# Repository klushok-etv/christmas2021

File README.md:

# christmas 2021
The PCB outline can be generated from the included svg file `star template` using the [svg2shenzen](https://github.com/badgeek/svg2shenzhen) plugin.

For the list of To-Do's check [the TODO list](https://github.com/klushok-etv/christmas2021/projects/1), feel free to add any issues or tasks as well!

## current idea
ESP12F has 15 (17 including rx tx) gpio available. There are 45 signals required to controll each color individually. By combining the same color every 5 leds, all leds can be controlled. Issue that remains is the current requirement per GPIO which far exceeds the limit of the pin.
The current can be increased by adding transistors/fets or something like 2 of the ULN2803 and common anode leds.

ESP kicad lib: [https://github.com/jdunmire/kicad-ESP8266](https://github.com/jdunmire/kicad-ESP8266). -> this library has most models but the centers of the pads are located in an odd place. the symbol is also not colored.

## Current design
This design makes use of the APA106 leds which are pincompatible with the pl9823 when pin 1 is attached to pin 4 etc. Both of these led types can be controlled as if they were a WS2812.

The two buttons are reset and io0, required for programming. 
IO0 can also be used as a user input pin.

THT components have been chosen where possible to easy soldering by hand. 
Components with a SMD package are still solderable by hand, using a tweezer is advised.

Power is fed through to the connectors at the top of the pcb, a jst or other connector can be soldered in place to ensure polarity is correct. No reverse polarity protection is in place!

The star can be programmed using the pads on the back. Wires can be soldered to the pads or pogo pins could be used.

The committee might make a custom programmer to ease flashing for the first time after which OTA/wifimanager can be uploaded. An anternative idea for the firmware might be [WLED](https://github.com/Aircoookie/WLED).

## Possible parts
- ESP32 wroom/wrover -> most expensive and biggest option but has plenty of IO, does require a pad to be soldered so hot air is required
- ESP01 -> very few pins but cheap
- ESP M3 -> based on the 8285 chip with low memory and only a few GPIO's but has a small footprint and is cheap
- ESP12F/E -> Good option but almost same price as ESP32 but reduced functionality and soon to be replaced by ESP32-C3 [https://www.aliexpress.com/item/32963951195.html](https://www.aliexpress.com/item/32963951195.html)
- pl9823 led [https://nl.aliexpress.com/item/32963082574.html](https://nl.aliexpress.com/item/32963082574.html)
- APA106 led [https://www.aliexpress.com/item/4001066329177.html](https://www.aliexpress.com/item/4001066329177.html) or diffused [https://www.aliexpress.com/item/32768672866.html](https://www.aliexpress.com/item/32768672866.html)
- buttons for reset and gpio0, 3x6x2.5mm: [https://www.aliexpress.com/item/32696590759.html](https://www.aliexpress.com/item/32696590759.html)
- angled clamp [https://www.aliexpress.com/item/1005002240862072.html](https://www.aliexpress.com/item/1005002240862072.html)
- usb c connectors [https://www.aliexpress.com/item/1005001283294686.html](https://www.aliexpress.com/item/1005001283294686.html)

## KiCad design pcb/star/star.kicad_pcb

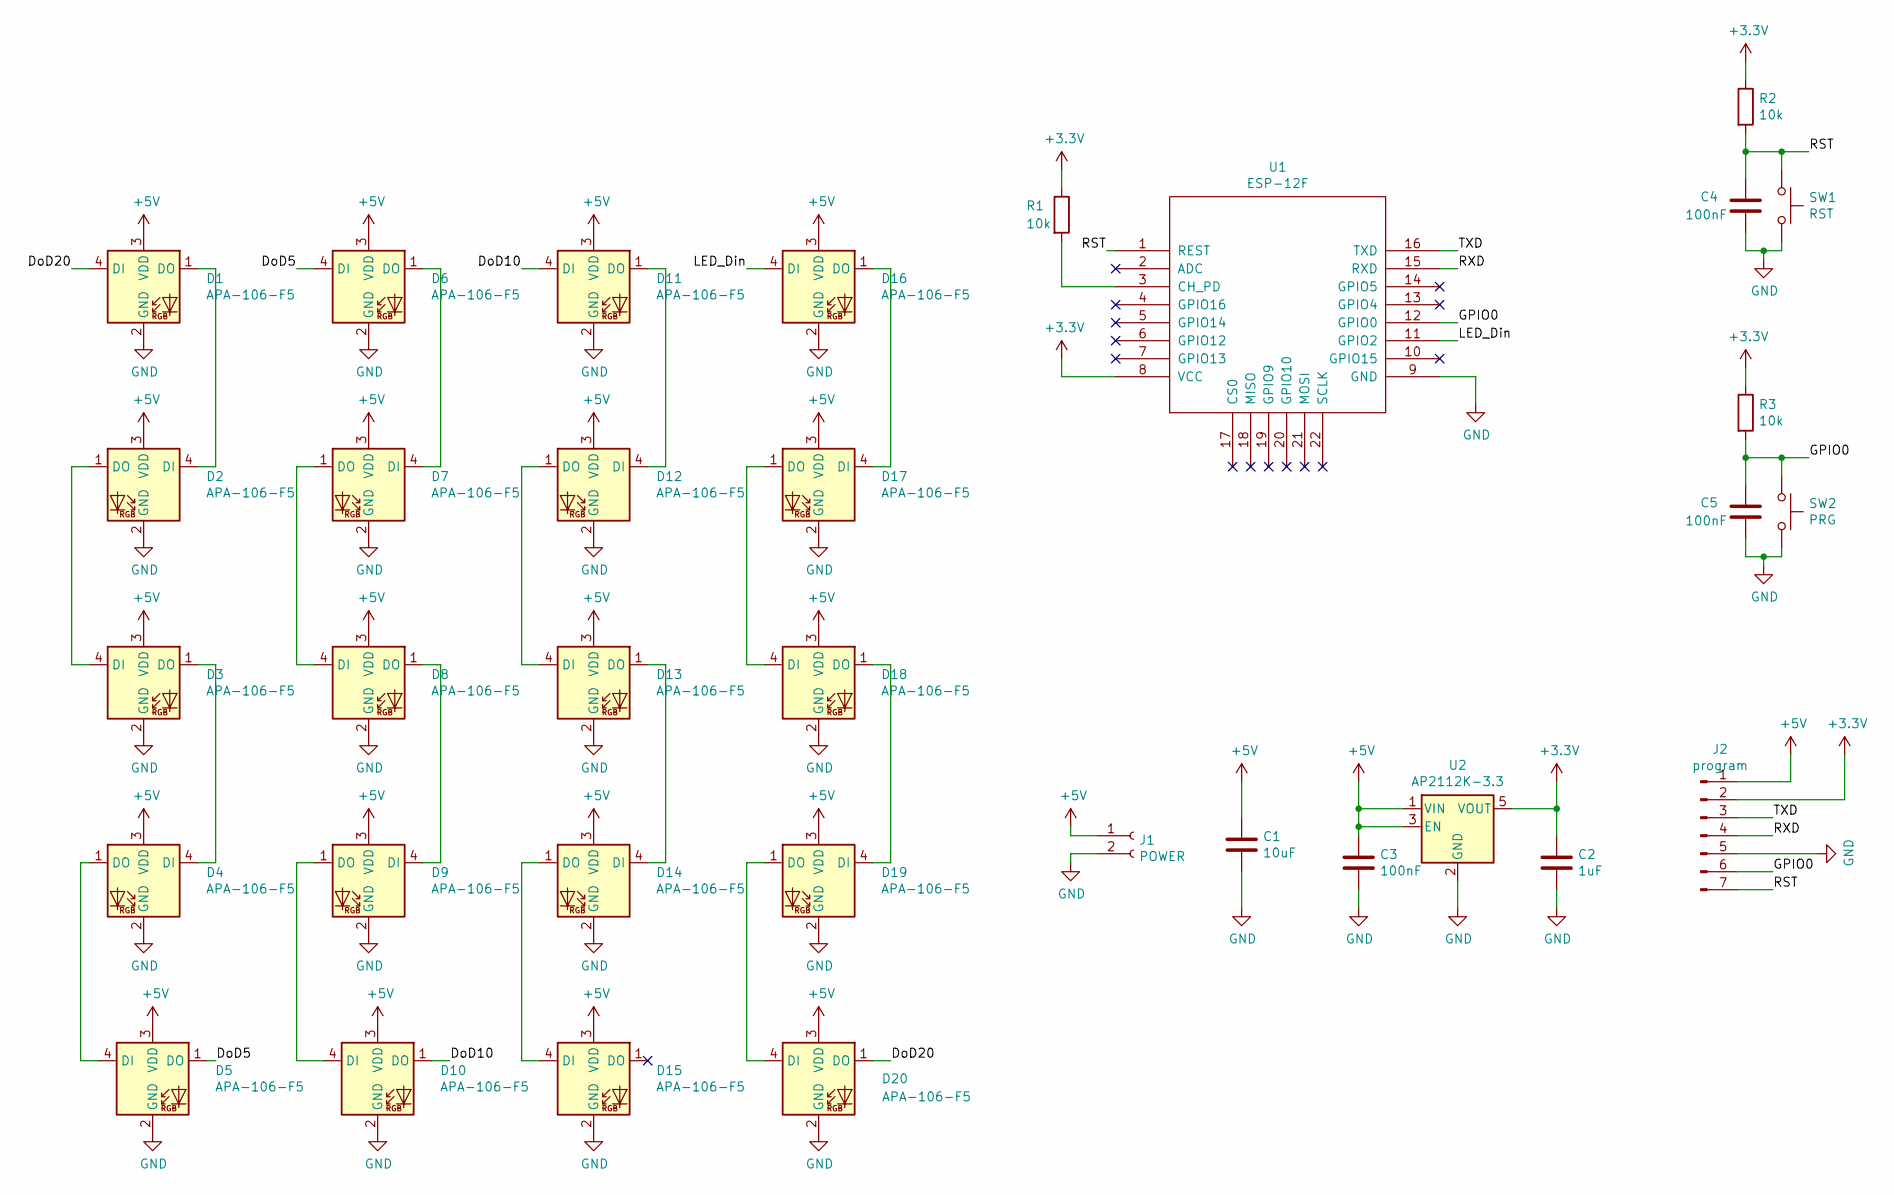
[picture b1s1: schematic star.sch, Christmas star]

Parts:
C1: 10uF; CP_Radial_D5.0mm_P2.50mm
C2: 1uF; CP_Radial_D5.0mm_P2.50mm
C3, C4, C5: 100nF; C_Disc_D5.0mm_W2.5mm_P2.50mm
D1, D2, D3, D4, D5, D6, D7, D8, D9, D10, D11, D12, D13, D14, D15, D16, D17, D18, D19, D20: APA-106-F5; LED_D5.0mm-4_RGB
J1: POWER; PinSocket_1x02_P2.54mm_Vertical
J2: program; conn_01x07_SMD
R1, R2, R3: 10k; R_Axial_DIN0204_L3.6mm_D1.6mm_P7.62mm_Horizontal
SW1: RST; SW_SPST_EVQPE1
SW2: PRG; SW_SPST_EVQPE1
U1: ESP-12F; ESP-12E_SMD
U2: AP2112K-3.3; SOT-23-5

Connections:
+3V3: C2.1, J2.2, R1.1, R2.1, R3.1, U1.8 (VCC), U2.5 (VOUT)
+5V: C1.1, C3.1, D1.3 (VDD), D2.3 (VDD), D3.3 (VDD), D4.3 (VDD), D5.3 (VDD), D6.3 (VDD), D7.3 (VDD), D8.3 (VDD), D9.3 (VDD), D10.3 (VDD), D11.3 (VDD), D12.3 (VDD), D13.3 (VDD), D14.3 (VDD), D15.3 (VDD), D16.3 (VDD), D17.3 (VDD), D18.3 (VDD), D19.3 (VDD), D20.3 (VDD), J1.1, J2.1, U2.1 (VIN), U2.3 (EN)
/DoD5: D5.1 (DO), D6.4 (DI)
/DoD10: D10.1 (DO), D11.4 (DI)
/DoD20: D1.4 (DI), D20.1 (DO)
/GPIO0: C5.2, J2.6, R3.2, SW2.1, U1.12 (GPIO0)
/LED_Din: D16.4 (DI), U1.11 (GPIO2)
/RST: C4.2, J2.7, R2.2, SW1.1, U1.1 (REST)
/RXD: J2.4, U1.15 (RXD)
/TXD: J2.3, U1.16 (TXD)
GND: C1.2, C2.2, C3.2, C4.1, C5.1, D1.2 (GND), D2.2 (GND), D3.2 (GND), D4.2 (GND), D5.2 (GND), D6.2 (GND), D7.2 (GND), D8.2 (GND), D9.2 (GND), D10.2 (GND), D11.2 (GND), D12.2 (GND), D13.2 (GND), D14.2 (GND), D15.2 (GND), D16.2 (GND), D17.2 (GND), D18.2 (GND), D19.2 (GND), D20.2 (GND), J1.2, J2.5, SW1.2, SW2.2, U1.9 (GND), U2.2 (GND)
unnamed: D1.1 (DO), D2.4 (DI)
unnamed: D2.1 (DO), D3.4 (DI)
unnamed: D3.1 (DO), D4.4 (DI)
unnamed: D4.1 (DO), D5.4 (DI)
unnamed: D6.1 (DO), D7.4 (DI)
unnamed: D7.1 (DO), D8.4 (DI)
unnamed: D8.1 (DO), D9.4 (DI)
unnamed: D9.1 (DO), D10.4 (DI)
unnamed: D11.1 (DO), D12.4 (DI)
unnamed: D12.1 (DO), D13.4 (DI)
unnamed: D13.1 (DO), D14.4 (DI)
unnamed: D14.1 (DO), D15.4 (DI)
unnamed: D16.1 (DO), D17.4 (DI)
unnamed: D17.1 (DO), D18.4 (DI)
unnamed: D18.1 (DO), D19.4 (DI)
unnamed: D19.1 (DO), D20.4 (DI)
unnamed: R1.2, U1.3 (CH_PD)

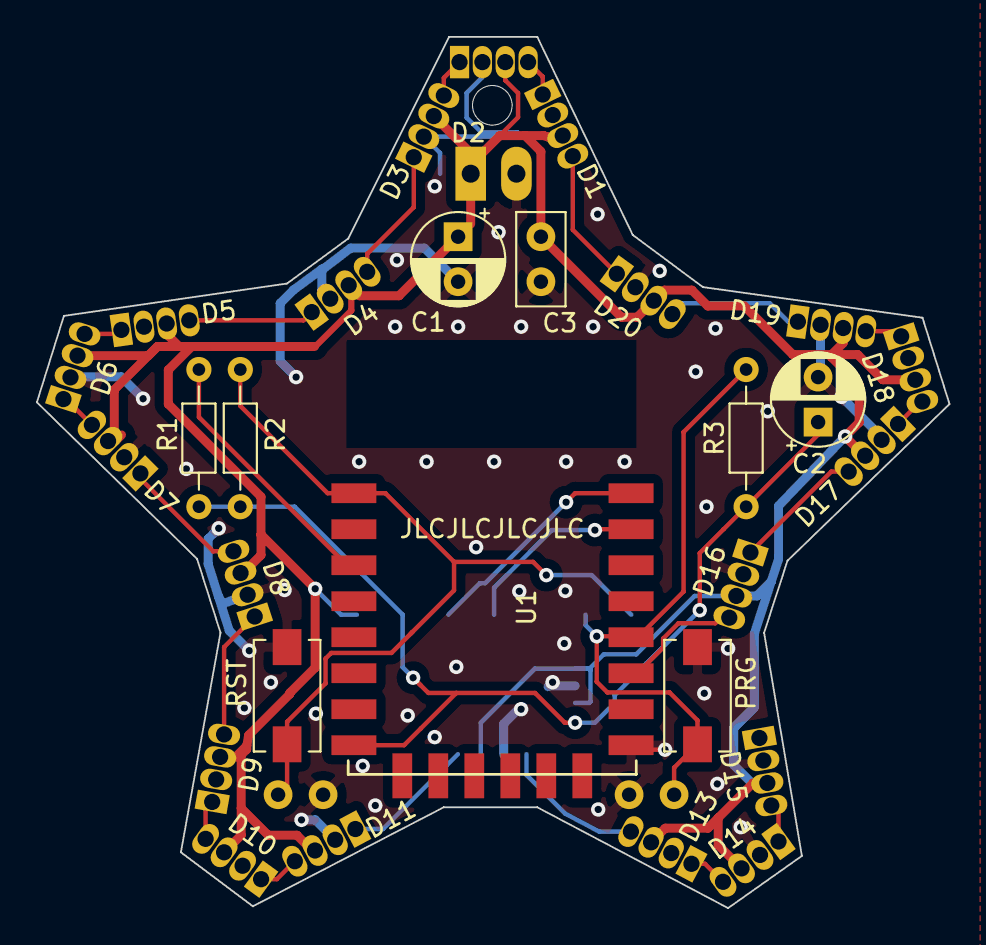
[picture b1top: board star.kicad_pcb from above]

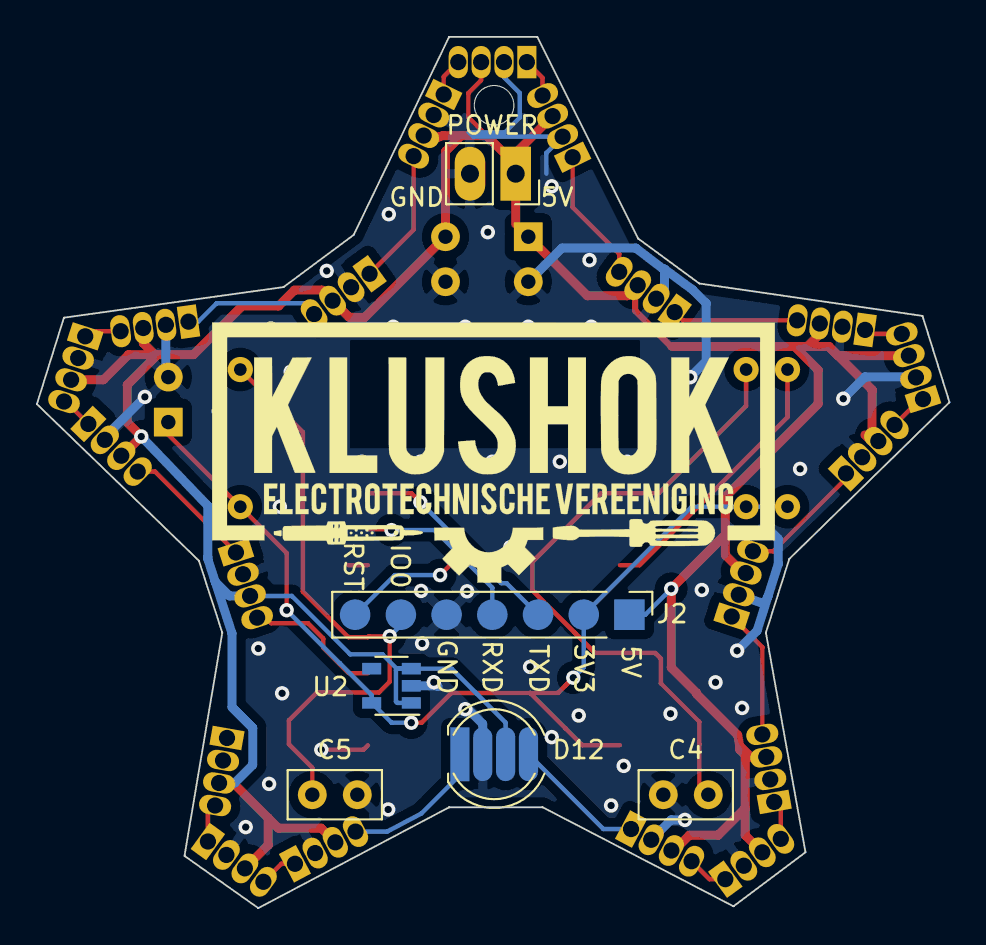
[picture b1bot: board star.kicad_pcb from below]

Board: 2 copper layers, 50.7 x 48.4 mm, 34 parts (6 on the bottom side), 28 nets.

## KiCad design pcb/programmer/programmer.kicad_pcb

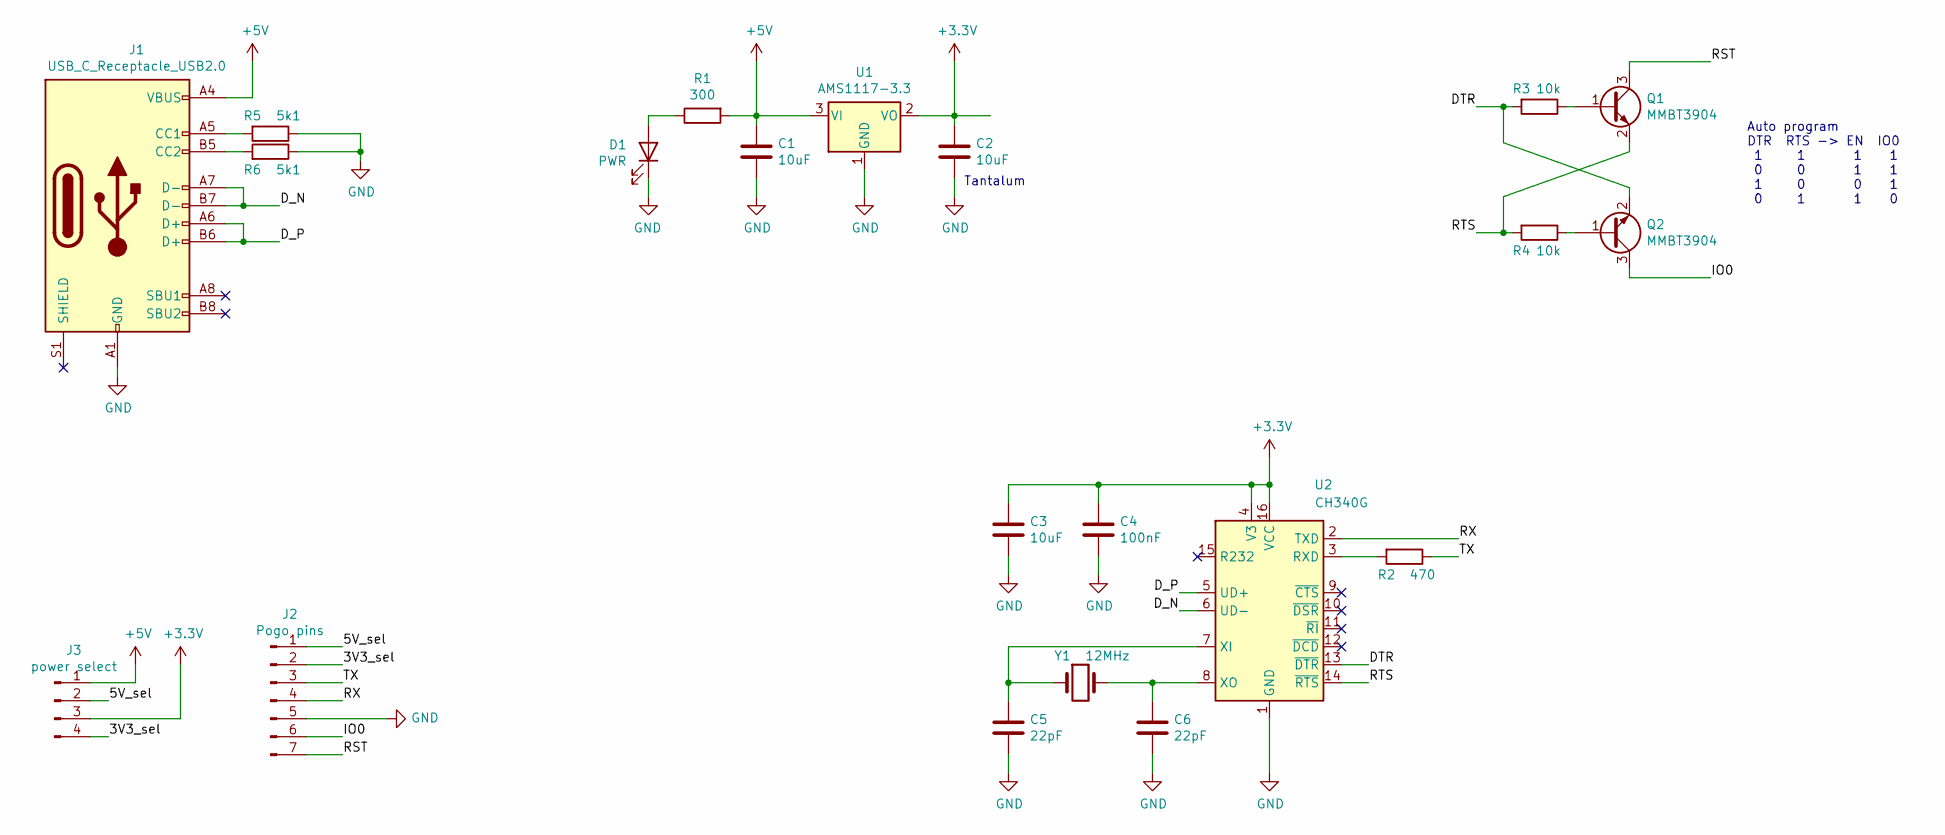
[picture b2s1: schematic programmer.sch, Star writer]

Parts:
C1, C3: 10uF; C_0805_2012Metric
C2: 10uF; CP_EIA-3216-10_Kemet-I
C4: 100nF; C_0805_2012Metric
C5, C6: 22pF; C_0805_2012Metric
D1: PWR; LED_1206_3216Metric
J1: USB_C_Receptacle_USB2.0; USB_C_Receptacle_HRO_TYPE-C-31-M-12
J2: Pogo pins; pogo_conn_01x07_oval
J3: power select; PinSocket_1x04_P2.54mm_Vertical
Q1, Q2: MMBT3904; SOT-23
R1: 300; R_0805_2012Metric
R2: 470; R_0805_2012Metric
R3, R4: 10k; R_0805_2012Metric
R5, R6: 5k1; R_0805_2012Metric
U1: AMS1117-3.3; SOT-223-3_TabPin2
U2: CH340G; SOIC-16_3.9x9.9mm_P1.27mm
Y1: 12MHz; Crystal_HC49-U_Vertical

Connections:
+3V3: C2.1, C3.1, C4.1, J3.3, U1.2 (VO), U2.4 (V3), U2.16 (VCC)
+5V: C1.1, J1.A4 (VBUS), J1.A9 (VBUS), J1.B4 (VBUS), J1.B9 (VBUS), J3.1, R1.2, U1.3 (VI)
/3V3_sel: J2.2, J3.4
/5V_sel: J2.1, J3.2
/DTR: Q2.2 (E), R3.2, U2.13 (~DTR)
/D_N: J1.A7 (D-), J1.B7 (D-), U2.6 (UD-)
/D_P: J1.A6 (D+), J1.B6 (D+), U2.5 (UD+)
/IO0: J2.6, Q2.3 (C)
/RST: J2.7, Q1.3 (C)
/RTS: Q1.2 (E), R4.2, U2.14 (~RTS)
/RX: J2.4, U2.2 (TXD)
/TX: J2.3, R2.1
GND: C1.2, C2.2, C3.2, C4.2, C5.2, C6.2, D1.1 (K), J1.A1 (GND), J1.A12 (GND), J1.B1 (GND), J1.B12 (GND), J2.5, R5.1, R6.1, U1.1 (GND), U2.1 (GND)
unnamed: C5.1, U2.7 (XI), Y1.1
unnamed: C6.1, U2.8 (XO), Y1.2
unnamed: D1.2 (A), R1.1
unnamed: J1.A5 (CC1), R5.2
unnamed: J1.B5 (CC2), R6.2
unnamed: Q1.1 (B), R3.1
unnamed: Q2.1 (B), R4.1
unnamed: R2.2, U2.3 (RXD)

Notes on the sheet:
Auto program DTR RTS -> EN IO0 1 1 1 1 0 0 1 1 1 0 0 1 0 1 1 0
Tantalum

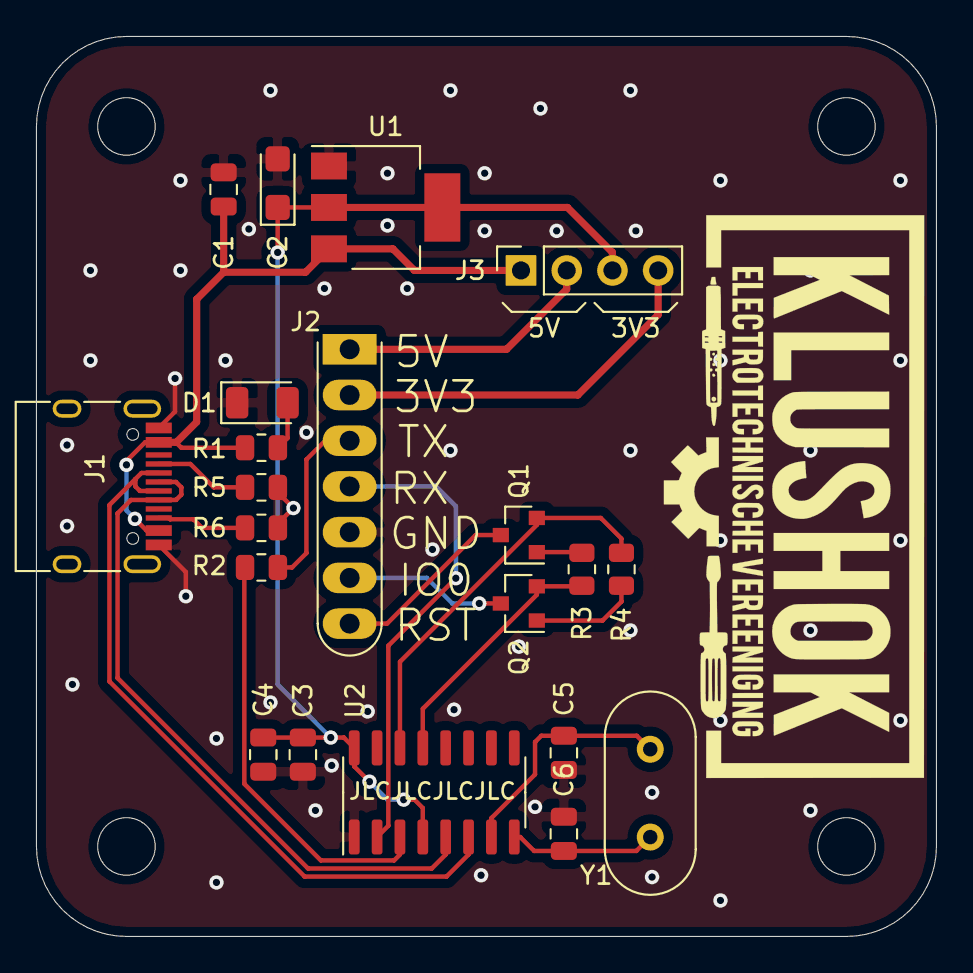
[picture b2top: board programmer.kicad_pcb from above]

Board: 2 copper layers, 50.0 x 50.0 mm, 22 parts (0 on the bottom side), 21 nets.

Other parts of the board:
Ref**: Val**; progpin_position_7pin

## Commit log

2021-09-01 inital idea
2021-09-02 outline increased
2021-09-02 apa106 and esp12f used
2021-09-02 ignore added
2021-09-02 gitignore implemented
2021-09-02 layout first pass done
2021-09-02 routing second pass
2021-09-02 current design shortly described
2021-09-02 schematic info added
2021-09-02 unsaved changes
2021-09-09 programmer and cad added
2021-09-09 gergers generated
2021-09-09 diffused leds added
2021-09-13 shipping added
2021-09-13 led pin changed to GPIO2
2021-09-18 poster mockup added
2021-09-29 poster mockup 2 added
2021-10-01 led placement image added
2021-10-11 ibom added
2021-10-11 manual added
2021-10-11 power source subsection added
2021-10-12 number of ceramic caps updated
2021-10-12 stencil holder added
